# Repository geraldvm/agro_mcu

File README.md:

# agro_mcu

[Diagramas](https://drive.google.com/file/d/1fX2lEoEfoRkMg510SkhPN9Y3XRPNFNjl/view?usp=sharing)

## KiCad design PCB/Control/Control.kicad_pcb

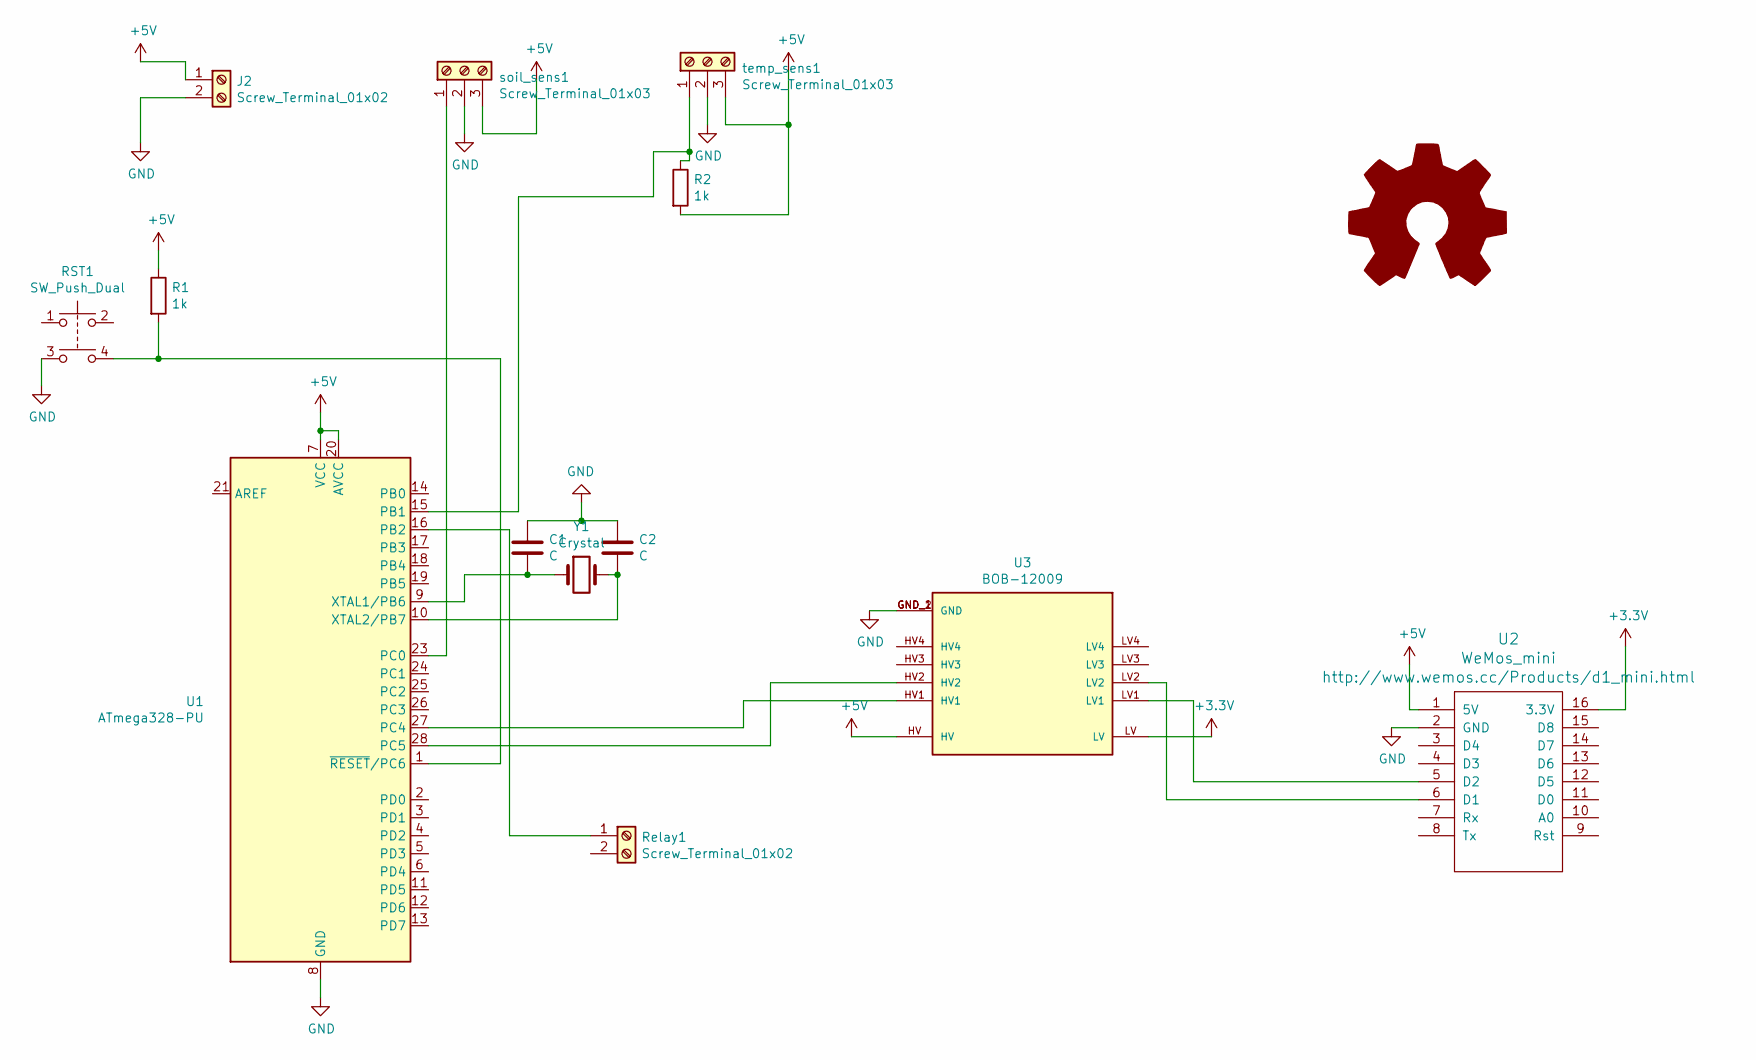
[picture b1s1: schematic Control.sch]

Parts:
C1, C2: C; C_Disc_D5.0mm_W2.5mm_P2.50mm
J2: Screw_Terminal_01x02; TerminalBlock_MetzConnect_Type094_RT03502HBLU_1x02_P5.00mm_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
R1, R2: 1k; R_Axial_DIN0411_L9.9mm_D3.6mm_P12.70mm_Horizontal
RST1: SW_Push_Dual; Push_E-Switch_KS01Q01
Relay1: Screw_Terminal_01x02; TerminalBlock_MetzConnect_Type055_RT01502HDWU_1x02_P5.00mm_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
U1: ATmega328-PU; DIP-28_W7.62mm
U2: WeMos_mini; WEMOS_D1_mini_light
U3: BOB-12009; CONV_BOB-12009; PARTREV 01
Y1: Crystal; Crystal_HC52-6mm_Vertical
soil_sens1: Screw_Terminal_01x03; TerminalBlock_MetzConnect_Type011_RT05503HBWC_1x03_P5.00mm_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
temp_sens1: Screw_Terminal_01x03; TerminalBlock_MetzConnect_Type011_RT05503HBWC_1x03_P5.00mm_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

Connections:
+3V3: U2.16 (3.3V), U3.LV
+5V: J2.1, R1.1, R2.2, U1.7 (VCC), U1.20 (AVCC), U2.1 (5V), U3.HV, soil_sens1.3, temp_sens1.3
GND: C1.1, C2.1, J2.2, RST1.3, U1.8 (GND), U1.22 (GND), U2.2 (GND), U3.GND_1 (GND), U3.GND_2 (GND), soil_sens1.2, temp_sens1.2
unnamed: C1.2, U1.9 (XTAL1/PB6), Y1.1
unnamed: C2.2, U1.10 (XTAL2/PB7), Y1.2
unnamed: R1.2, RST1.4, U1.1 (~RESET~/PC6)
unnamed: R2.1, U1.15 (PB1), temp_sens1.1
unnamed: Relay1.1, U1.16 (PB2)
unnamed: U1.23 (PC0), soil_sens1.1
unnamed: U1.27 (PC4), U3.HV1
unnamed: U1.28 (PC5), U3.HV2
unnamed: U2.5 (D2), U3.LV1
unnamed: U2.6 (D1), U3.LV2

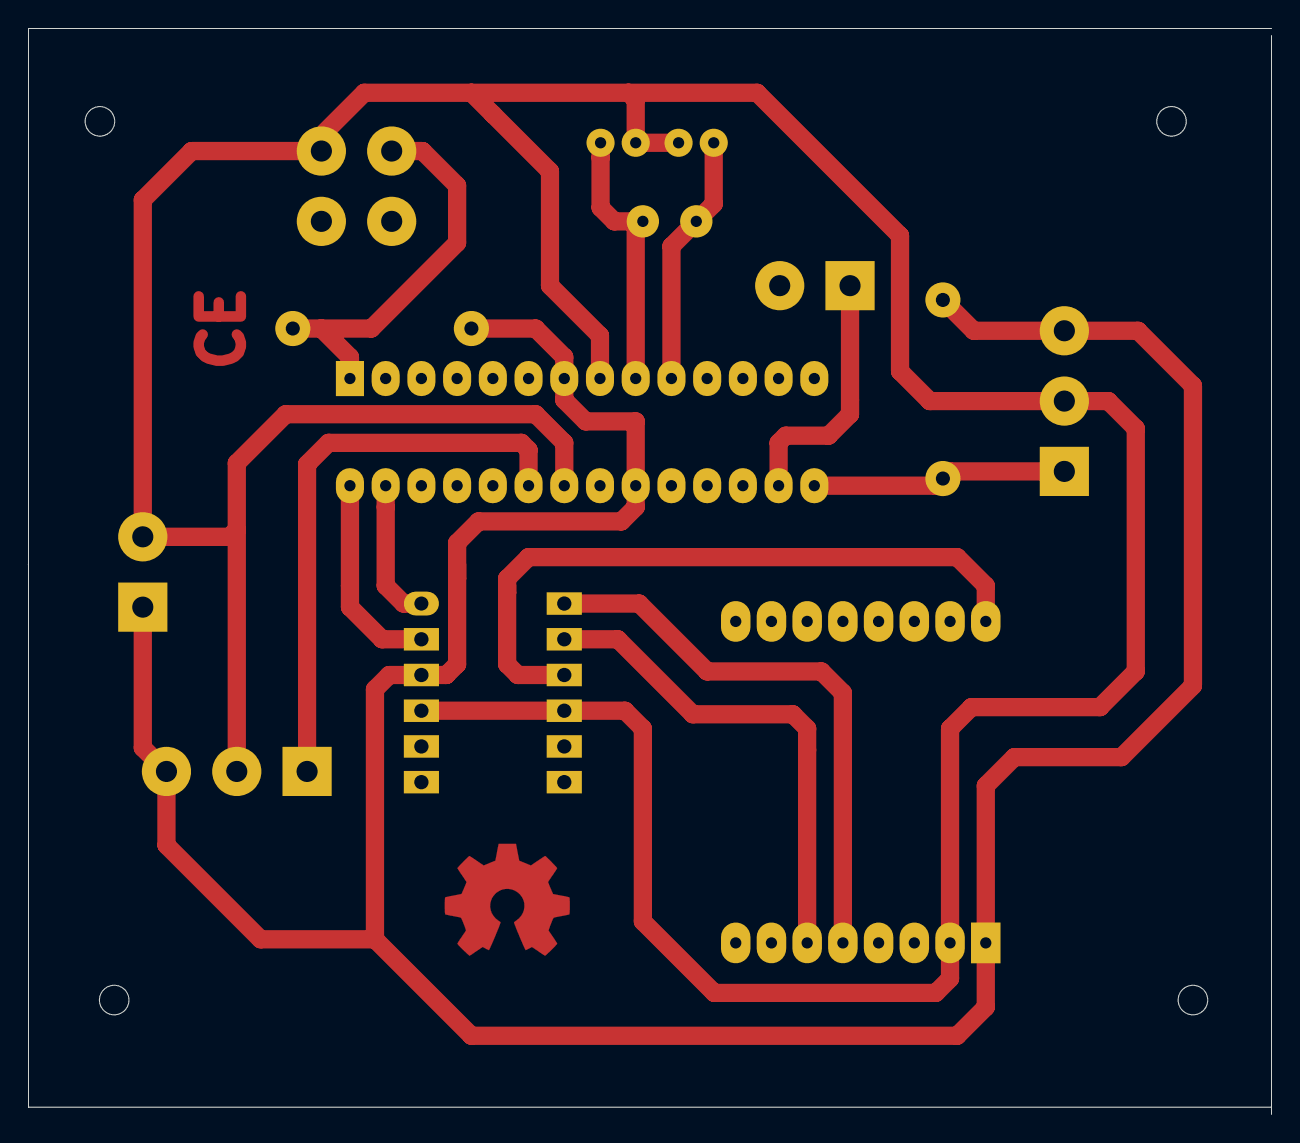
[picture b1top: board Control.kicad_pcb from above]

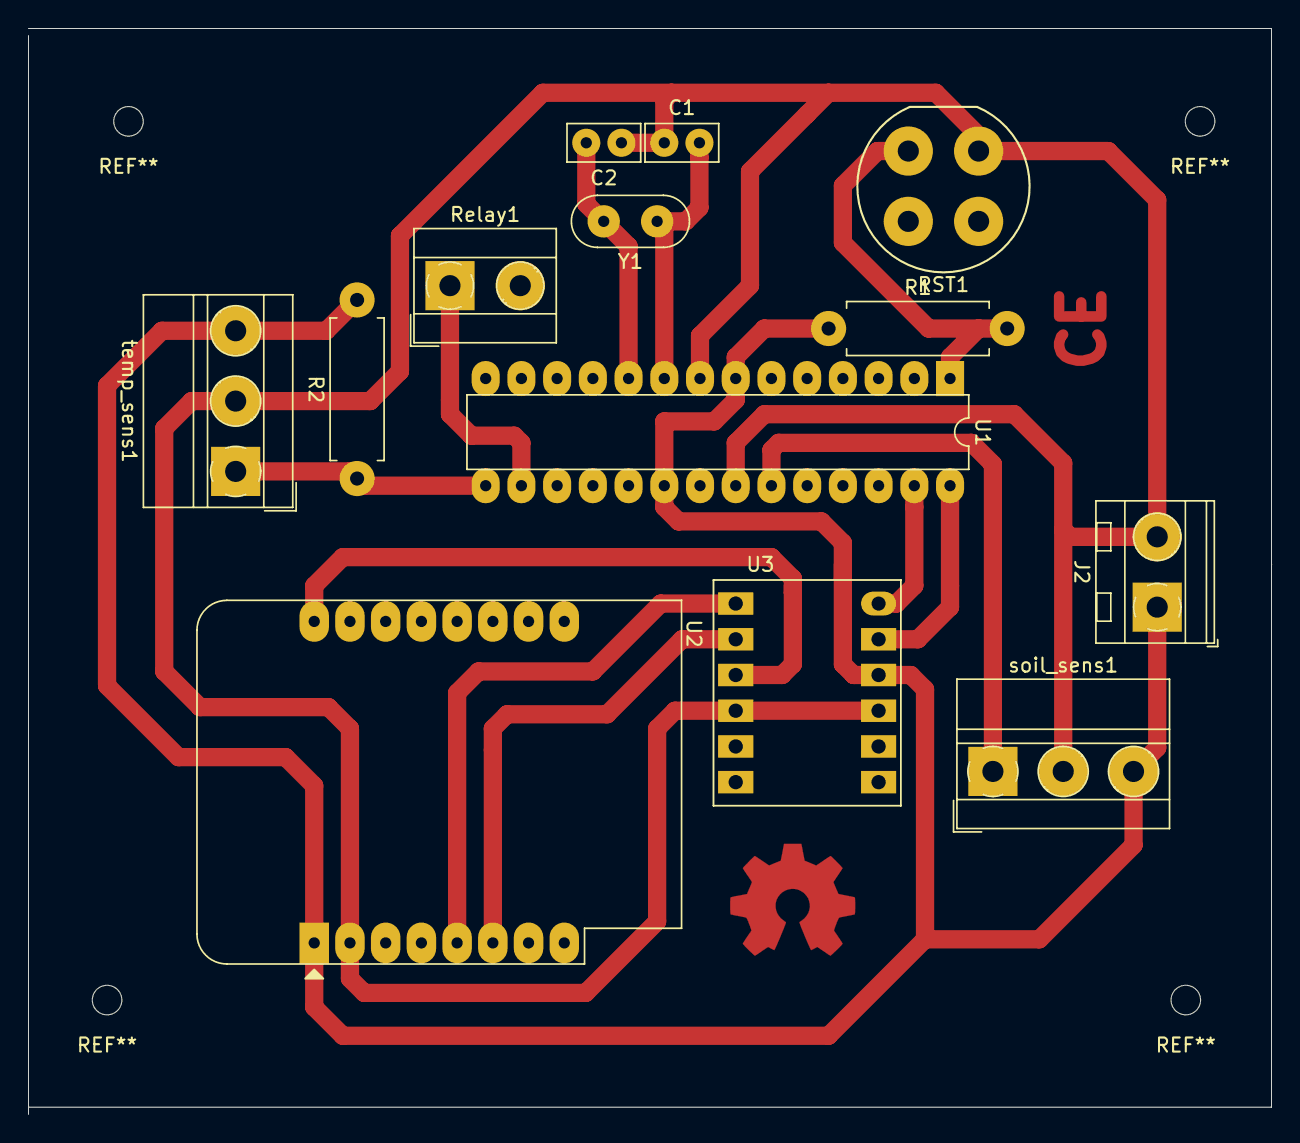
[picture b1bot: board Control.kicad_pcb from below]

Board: 2 copper layers, 88.4 x 77.2 mm, 13 parts (13 on the bottom side), 13 nets.

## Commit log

2022-05-23 Example: Python API
2022-05-23 Example: PostgresSQL
2022-05-23 Example: NodeJS API
2022-05-23 API modules
2022-05-23 NodeJS API
2022-05-23 Examples
2022-05-24 Design
2022-05-25 Get Address Temperature Sensor
2022-05-25 Temperature Sensor Code
2022-05-25 Soil Moisture
2022-06-12 Codigo de pruebas
2022-06-12 Codigo para master Wifi Module y para un dummy slave
2022-06-12 AWS Connection
2022-06-13 Get and Insert for Measure and DataPar
2022-06-14 Uniendo mediciones
2022-06-14 Get by ID in Measure and Put in DataPar
2022-06-15 Enviando json array through MQTT
2022-06-16 Add basic frontend views
2022-06-16 Add models curso->medida, laboratorio->datapar
2022-06-17 servicio curso -> servicio para medidas
2022-06-17 Last change
2022-11-12 Database for measures
2022-11-12 Remove files
2022-11-12 MQTT Arduino Client
